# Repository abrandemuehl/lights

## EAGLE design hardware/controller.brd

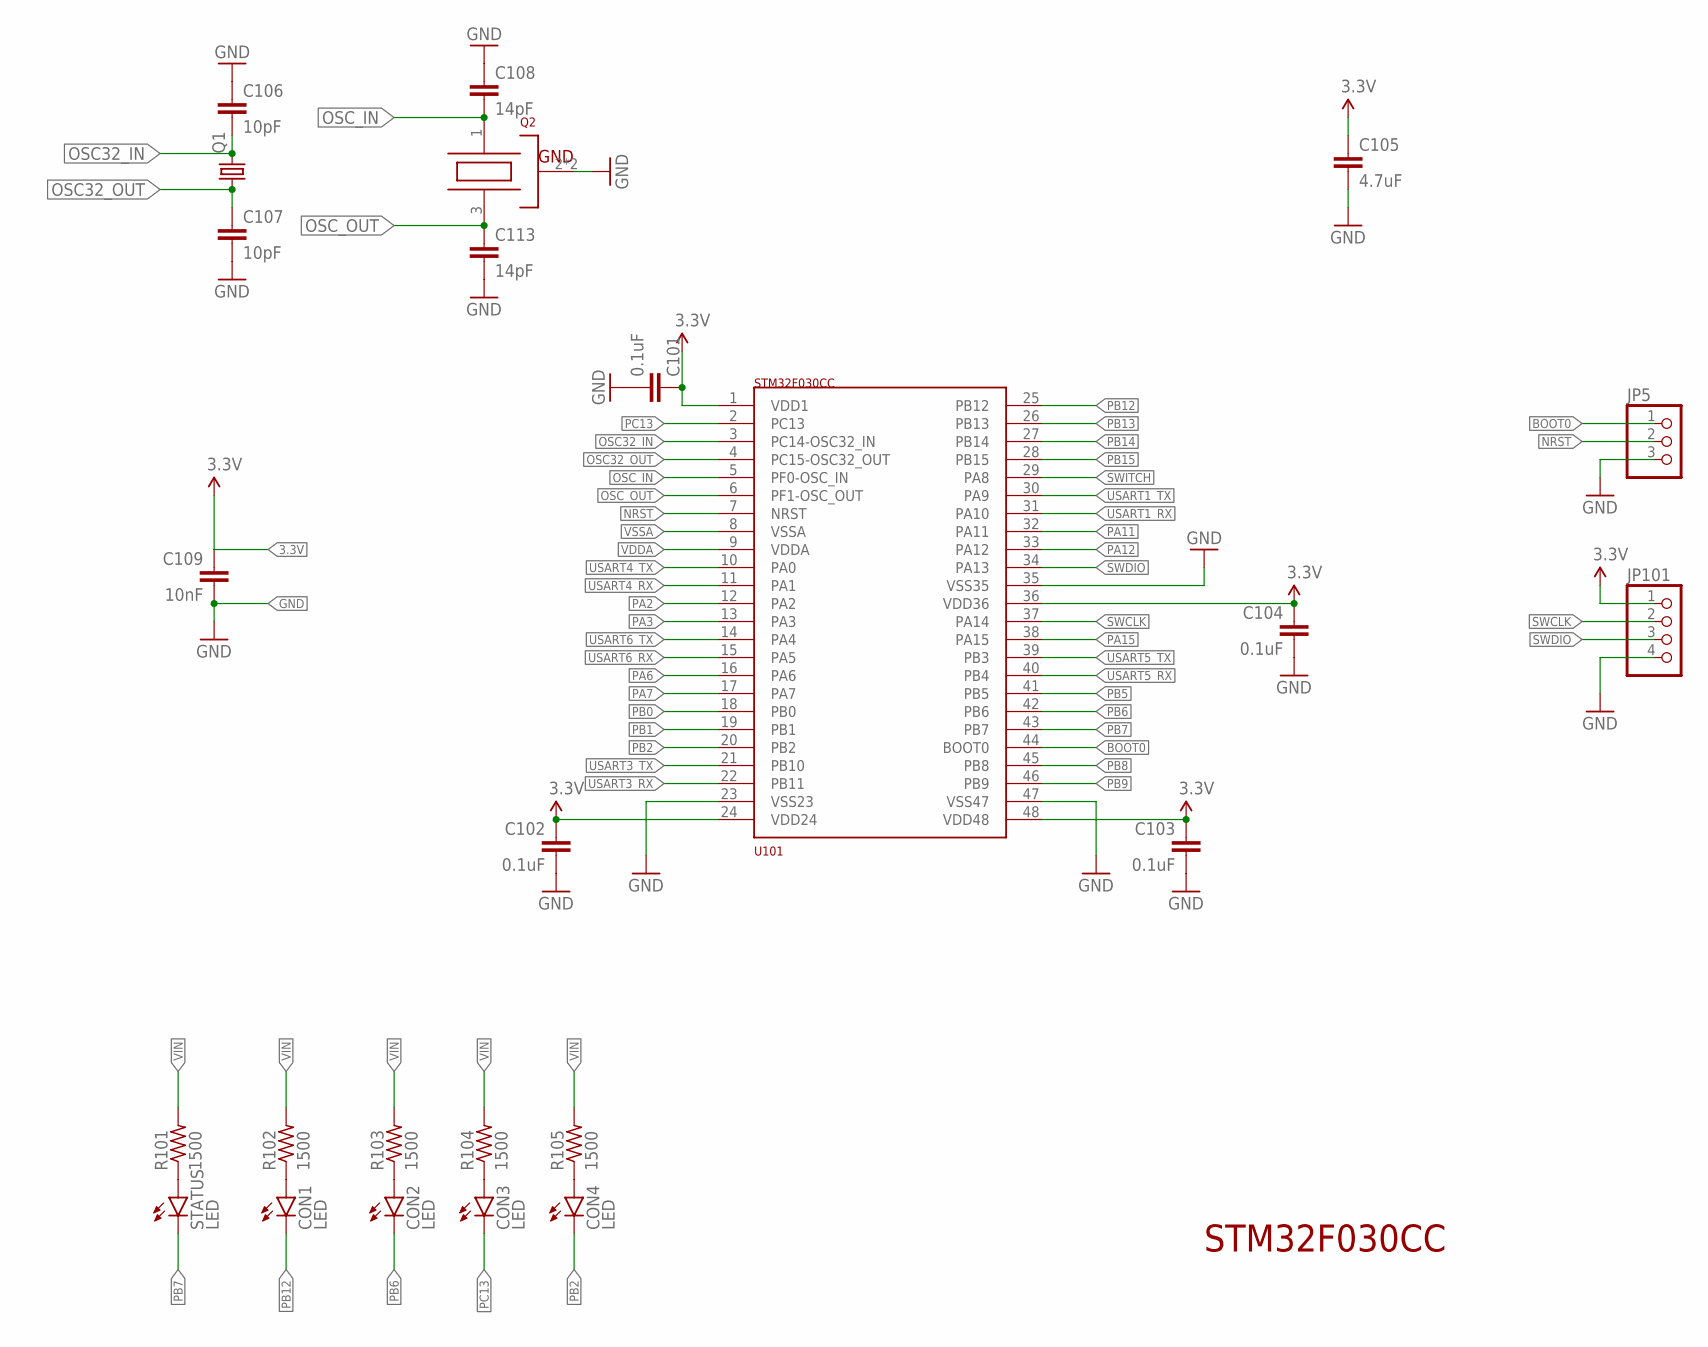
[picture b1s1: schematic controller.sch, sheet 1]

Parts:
C101, C102, C103, C104: 0.1uF; 0603-CAP
C105: 4.7uF; 0603-CAP
C106, C107: 10pF; 0603-CAP
C108, C113: 14pF; 0603-CAP
C109: 10nF; 0603-CAP
CON1, CON2, CON3, CON4: LED; LED-0603
JP5: PINHD-1X3; 1X03
JP101: PINHD-1X4; 1X04
Q1: CRYSTALFC1610AN; FC1610AN
Q2: OSCILLATOR; OSC3.2X2.5
R101, R102, R103, R104, R105: 1500; R0603
STATUS: LED; LED-0603
U101: STM32F030CC

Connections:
3.3V: C101.1, C102.1, C103.1, C104.1, C105.1, C109.1, JP101.1, U101.1 (VDD1), U101.24 (VDD24), U101.36 (VDD36), U101.48 (VDD48); also elsewhere on the board
BOOT0: JP5.1, U101.44 (BOOT0); also elsewhere on the board
GND: C101.2, C102.2, C103.2, C104.2, C105.2, C106.1, C107.2, C108.1, C109.2, C113.2, JP5.3, JP101.4, Q2.2 (GND), Q2.4 (GND), U101.23 (VSS23), U101.35 (VSS35), U101.47 (VSS47); also elsewhere on the board
unnamed: R101.1, STATUS.A
unnamed: CON1.A, R102.1
unnamed: CON2.A, R103.1
unnamed: CON3.A, R104.1
unnamed: CON4.A, R105.1
NRST: JP5.2, U101.7 (NRST); also elsewhere on the board
OSC32_IN: C106.2, Q1.2, U101.3 (PC14-OSC32_IN)
OSC32_OUT: C107.1, Q1.1, U101.4 (PC15-OSC32_OUT)
OSC_IN: C108.2, Q2.1 (OSC1), U101.5 (PF0-OSC_IN)
OSC_OUT: C113.1, Q2.3 (OSC2), U101.6 (PF1-OSC_OUT)
PA2: U101.12 (PA2)
PA3: U101.13 (PA3)
PA6: U101.16 (PA6)
PA7: U101.17 (PA7)
PA11: U101.32 (PA11)
PA12: U101.33 (PA12)
PA15: U101.38 (PA15)
PB0: U101.18 (PB0)
PB1: U101.19 (PB1)
PB2: CON4.C, U101.20 (PB2)
PB5: U101.41 (PB5)
PB6: CON2.C, U101.42 (PB6)
PB7: STATUS.C, U101.43 (PB7)
PB8: U101.45 (PB8)
PB9: U101.46 (PB9)
PB12: CON1.C, U101.25 (PB12)
PB13: U101.26 (PB13)
PB14: U101.27 (PB14)
PB15: U101.28 (PB15)
PC13: CON3.C, U101.2 (PC13)
SWCLK: JP101.2, U101.37 (PA14)
SWDIO: JP101.3, U101.34 (PA13)
SWITCH: U101.29 (PA8); also elsewhere on the board
USART1_RX: U101.31 (PA10); also elsewhere on the board
USART1_TX: U101.30 (PA9); also elsewhere on the board
USART3_RX: U101.22 (PB11); also elsewhere on the board
USART3_TX: U101.21 (PB10); also elsewhere on the board
USART4_RX: U101.11 (PA1); also elsewhere on the board
USART4_TX: U101.10 (PA0); also elsewhere on the board
USART5_RX: U101.40 (PB4); also elsewhere on the board
USART5_TX: U101.39 (PB3); also elsewhere on the board
USART6_RX: U101.15 (PA5); also elsewhere on the board
USART6_TX: U101.14 (PA4); also elsewhere on the board
VDDA: U101.9 (VDDA)
VIN: R101.2, R102.2, R103.2, R104.2, R105.2; also elsewhere on the board
VSSA: U101.8 (VSSA)

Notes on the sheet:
STM32F030CC

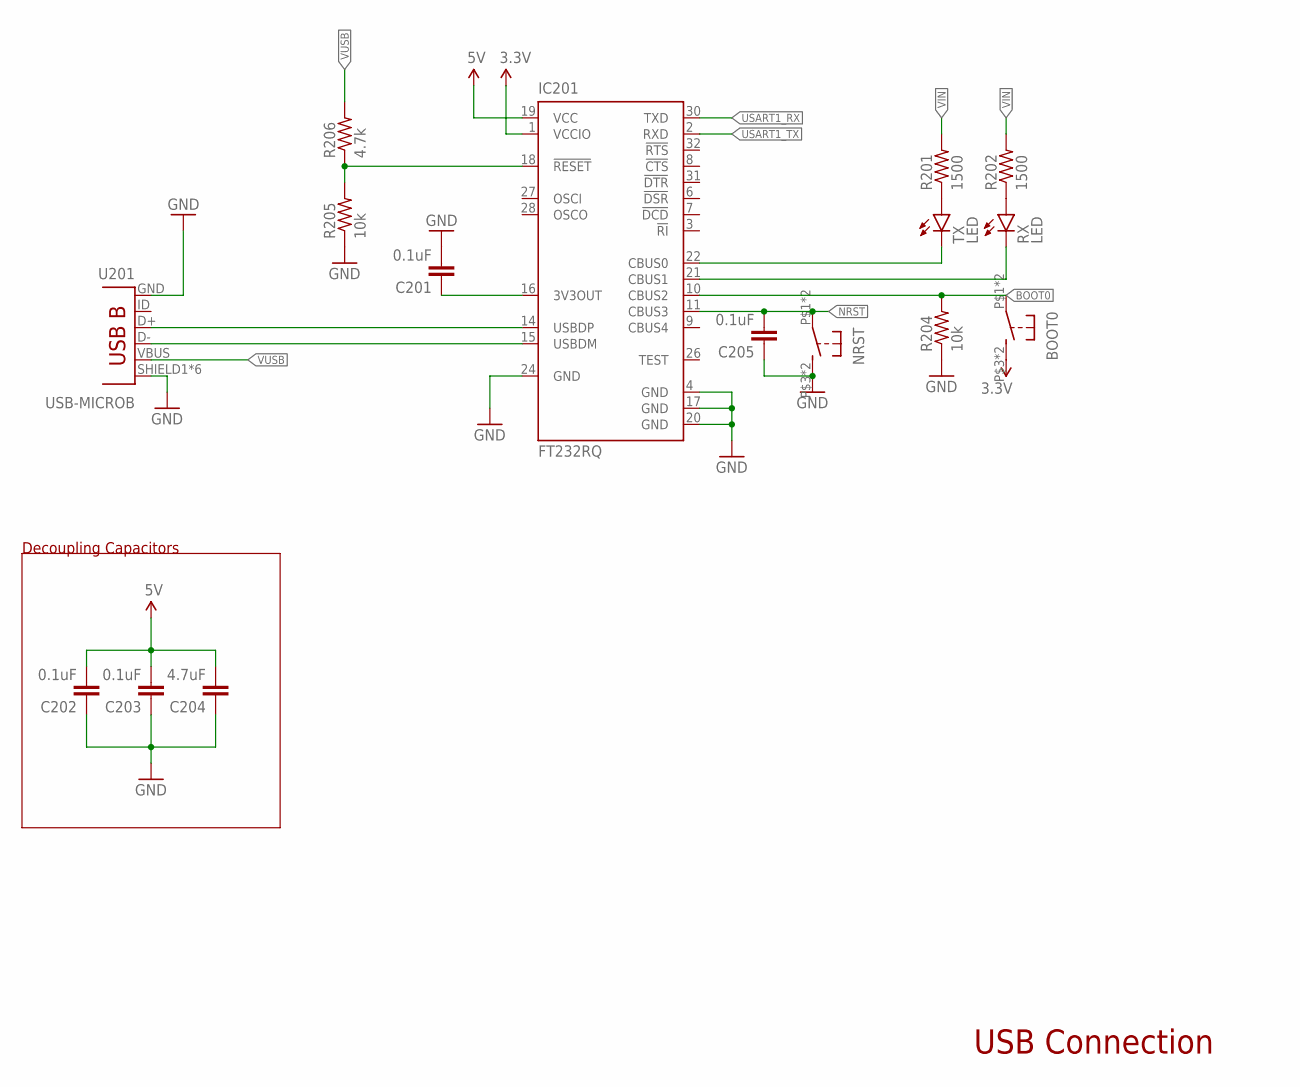
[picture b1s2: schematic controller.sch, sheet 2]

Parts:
BOOT0: BUTTON_MOMENTARY4P; BUTTON_MOMENTARY_KMR211G
C201, C202, C203, C205: 0.1uF; 0603-CAP
C204: 4.7uF; 0603-CAP
IC201: FT232RQ; QFN32
NRST: BUTTON_MOMENTARY4P; BUTTON_MOMENTARY_KMR211G
R201, R202: 1500; R0603
R204, R205: 10k; R0603
R206: 4.7k; R0603
RX: LED; LED-0603
TX: LED; LED-0603
U201: USB-MICROB; USB-B-MICRO-SMD

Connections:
3.3V: BOOT0.P$3 (S), BOOT0.P$4 (S), IC201.1 (VCCIO); also elsewhere on the board
5V: C202.2, C203.2, C204.2, IC201.19 (VCC); also elsewhere on the board
BOOT0: BOOT0.P$1, BOOT0.P$2, IC201.10 (CBUS2), R204.2; also elsewhere on the board
GND: C201.2, C202.1, C203.1, C204.1, C205.1, IC201.4 (GND), IC201.17 (GND), IC201.20 (GND), IC201.24 (GND), NRST.P$3 (S), NRST.P$4 (S), R204.1, R205.1, U201.GND, U201.SHIELD1 (SHIELD), U201.SHIELD2 (SHIELD), U201.SHIELD3 (SHIELD), U201.SHIELD4 (SHIELD), U201.SHIELD5 (SHIELD), U201.SHIELD6 (SHIELD); also elsewhere on the board
unnamed: IC201.18 (!RESET), R205.2, R206.1
unnamed: C201.1, IC201.16 (3V3OUT)
unnamed: R202.1, RX.A
unnamed: R201.1, TX.A
NRST: C205.2, IC201.11 (CBUS3), NRST.P$1, NRST.P$2; also elsewhere on the board
RX_LED: IC201.21 (CBUS1), RX.C
TX_LED: IC201.22 (CBUS0), TX.C
USART1_RX: IC201.30 (TXD); also elsewhere on the board
USART1_TX: IC201.2 (RXD); also elsewhere on the board
USBDM: IC201.15 (USBDM), U201.D-
USBDP: IC201.14 (USBDP), U201.D+
VIN: R201.2, R202.2; also elsewhere on the board
VUSB: R206.2, U201.VBUS

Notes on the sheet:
USB Connection
Decoupling Capacitors

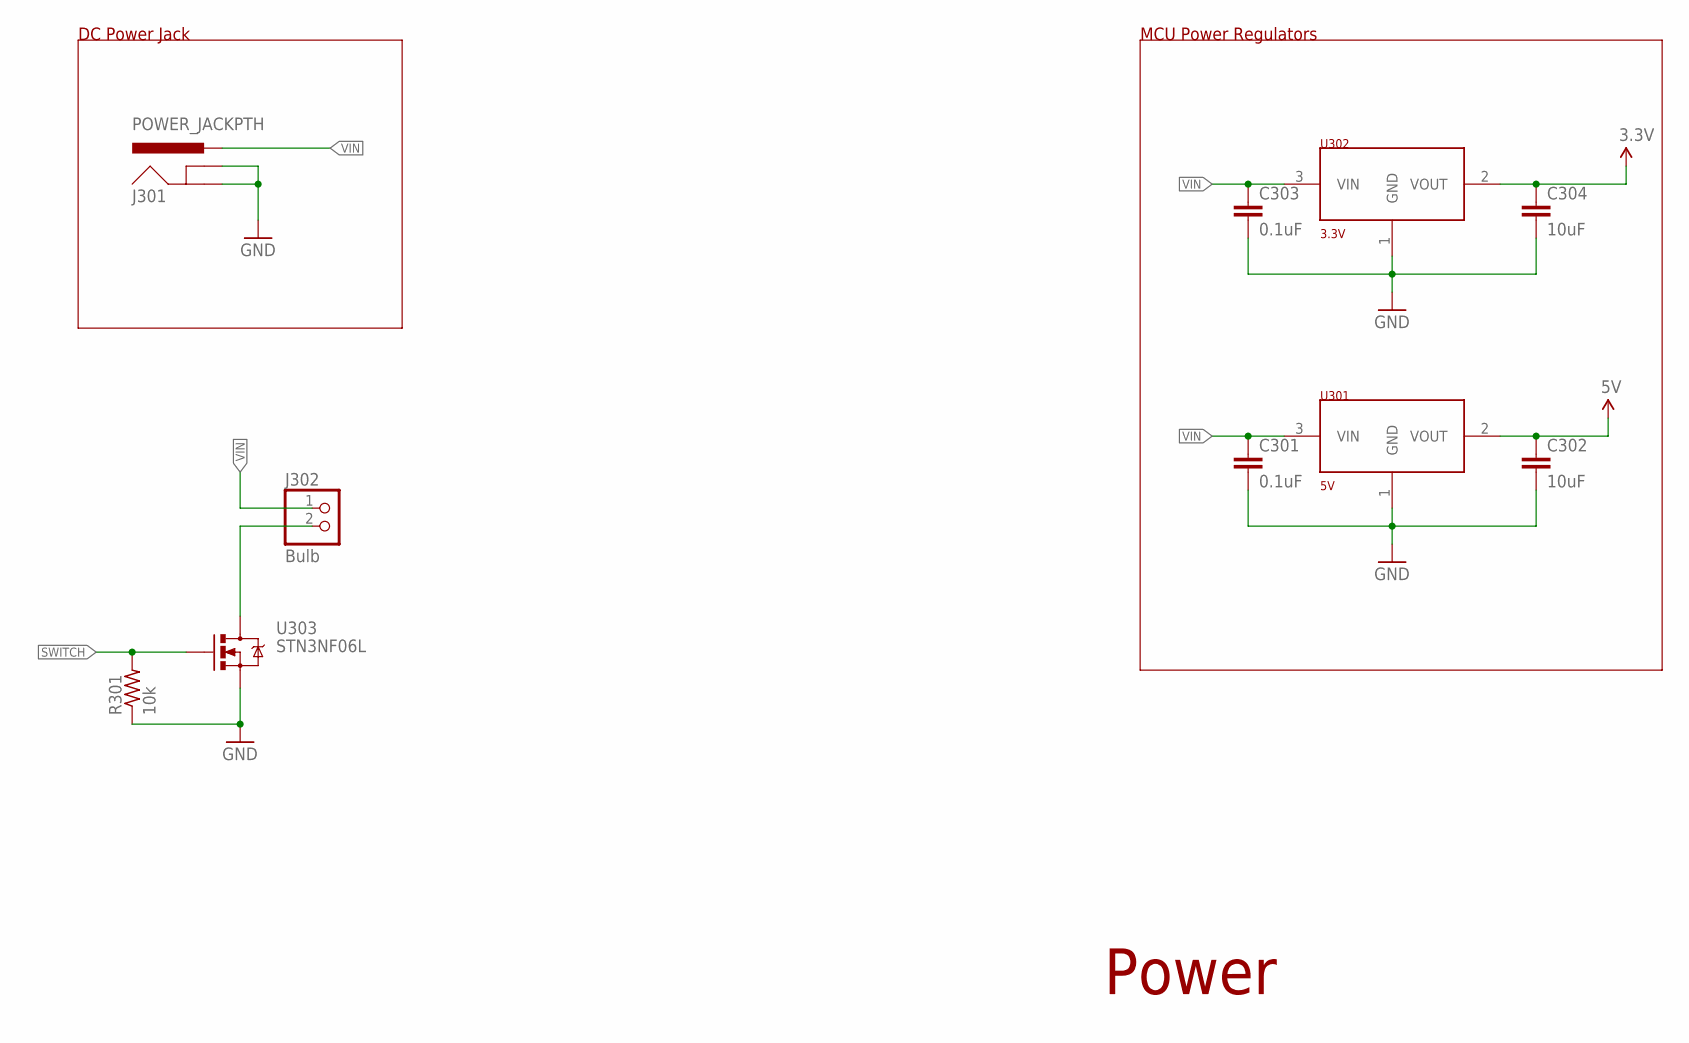
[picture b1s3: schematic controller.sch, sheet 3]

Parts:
C301, C303: 0.1uF; 0603-CAP
C302, C304: 10uF; 0603-CAP
J301: POWER_JACKPTH; POWER_JACK_PTH
J302: Bulb; 1X02
R301: 10k; R0603
U301: 5V; SOT223
U302: 3.3V; SOT223
U303: STN3NF06L; SOT223

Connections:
3.3V: C304.1, U302.2 (VOUT); also elsewhere on the board
5V: C302.1, U301.2 (VOUT); also elsewhere on the board
BULB: J302.2, U303.2 (D), U303.4 (D)
GND: C301.2, C302.2, C303.2, C304.2, J301.GND, J301.GNDBREAK, R301.1, U301.1 (GND), U302.1 (GND), U303.3 (S); also elsewhere on the board
SWITCH: R301.2, U303.1 (G); also elsewhere on the board
VIN: C301.1, C303.1, J301.PWR, J302.1, U301.3 (VIN), U302.3 (VIN); also elsewhere on the board

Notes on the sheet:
Power
MCU Power Regulators
DC Power Jack

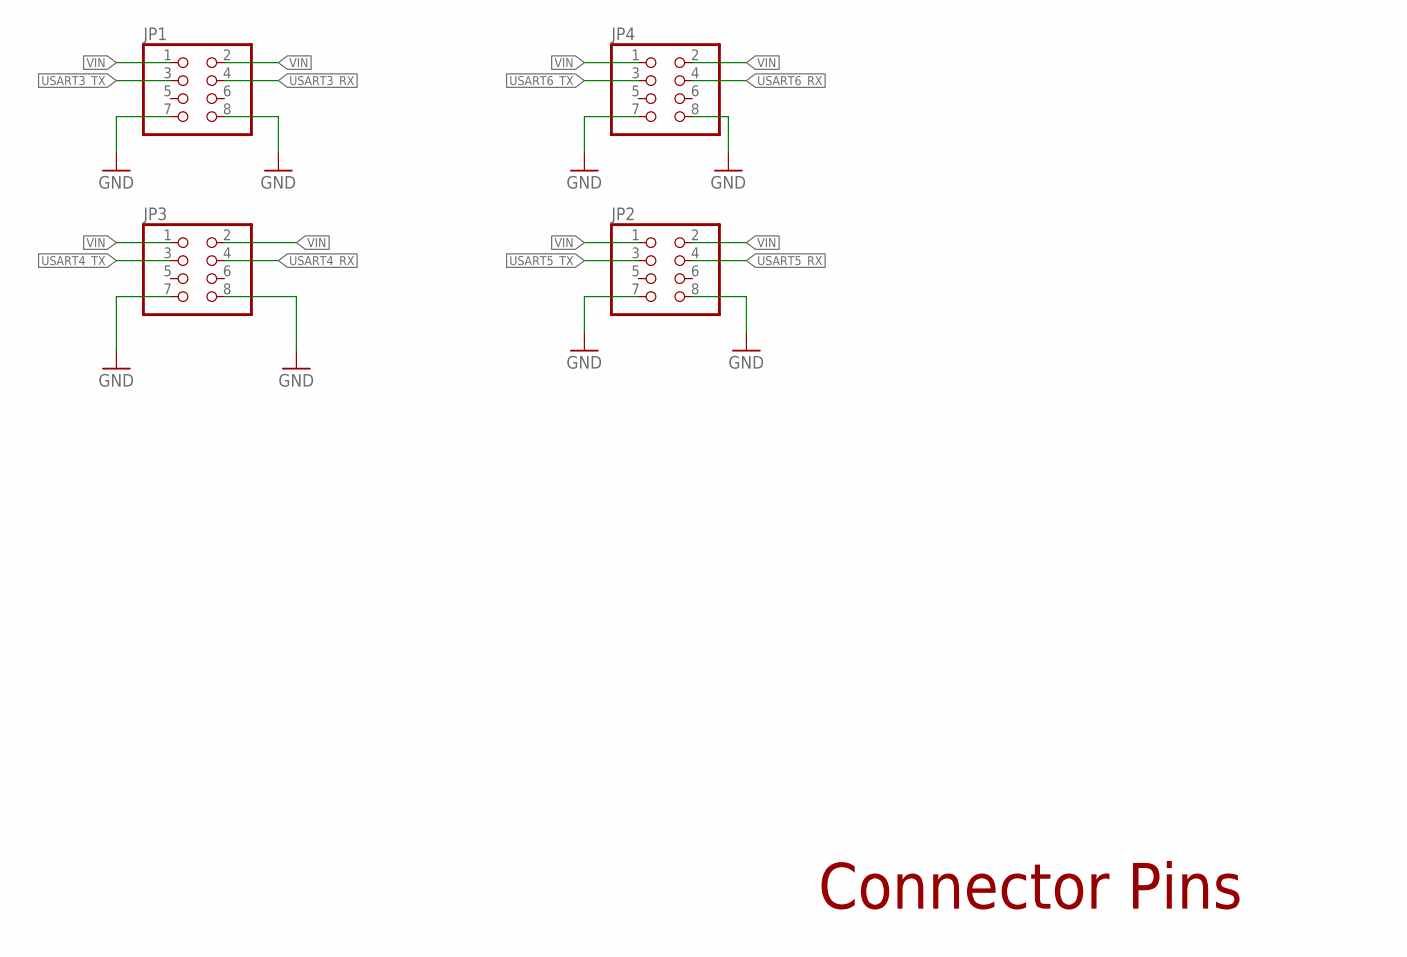
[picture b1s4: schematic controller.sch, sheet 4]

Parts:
JP1, JP2, JP3, JP4: PINHD-2X4; 2X04

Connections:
GND: JP1.7, JP1.8, JP2.7, JP2.8, JP3.7, JP3.8, JP4.7, JP4.8; also elsewhere on the board
USART3_RX: JP1.4; also elsewhere on the board
USART3_TX: JP1.3; also elsewhere on the board
USART4_RX: JP3.4; also elsewhere on the board
USART4_TX: JP3.3; also elsewhere on the board
USART5_RX: JP2.4; also elsewhere on the board
USART5_TX: JP2.3; also elsewhere on the board
USART6_RX: JP4.4; also elsewhere on the board
USART6_TX: JP4.3; also elsewhere on the board
VIN: JP1.1, JP1.2, JP2.1, JP2.2, JP3.1, JP3.2, JP4.1, JP4.2; also elsewhere on the board

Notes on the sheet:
Connector Pins

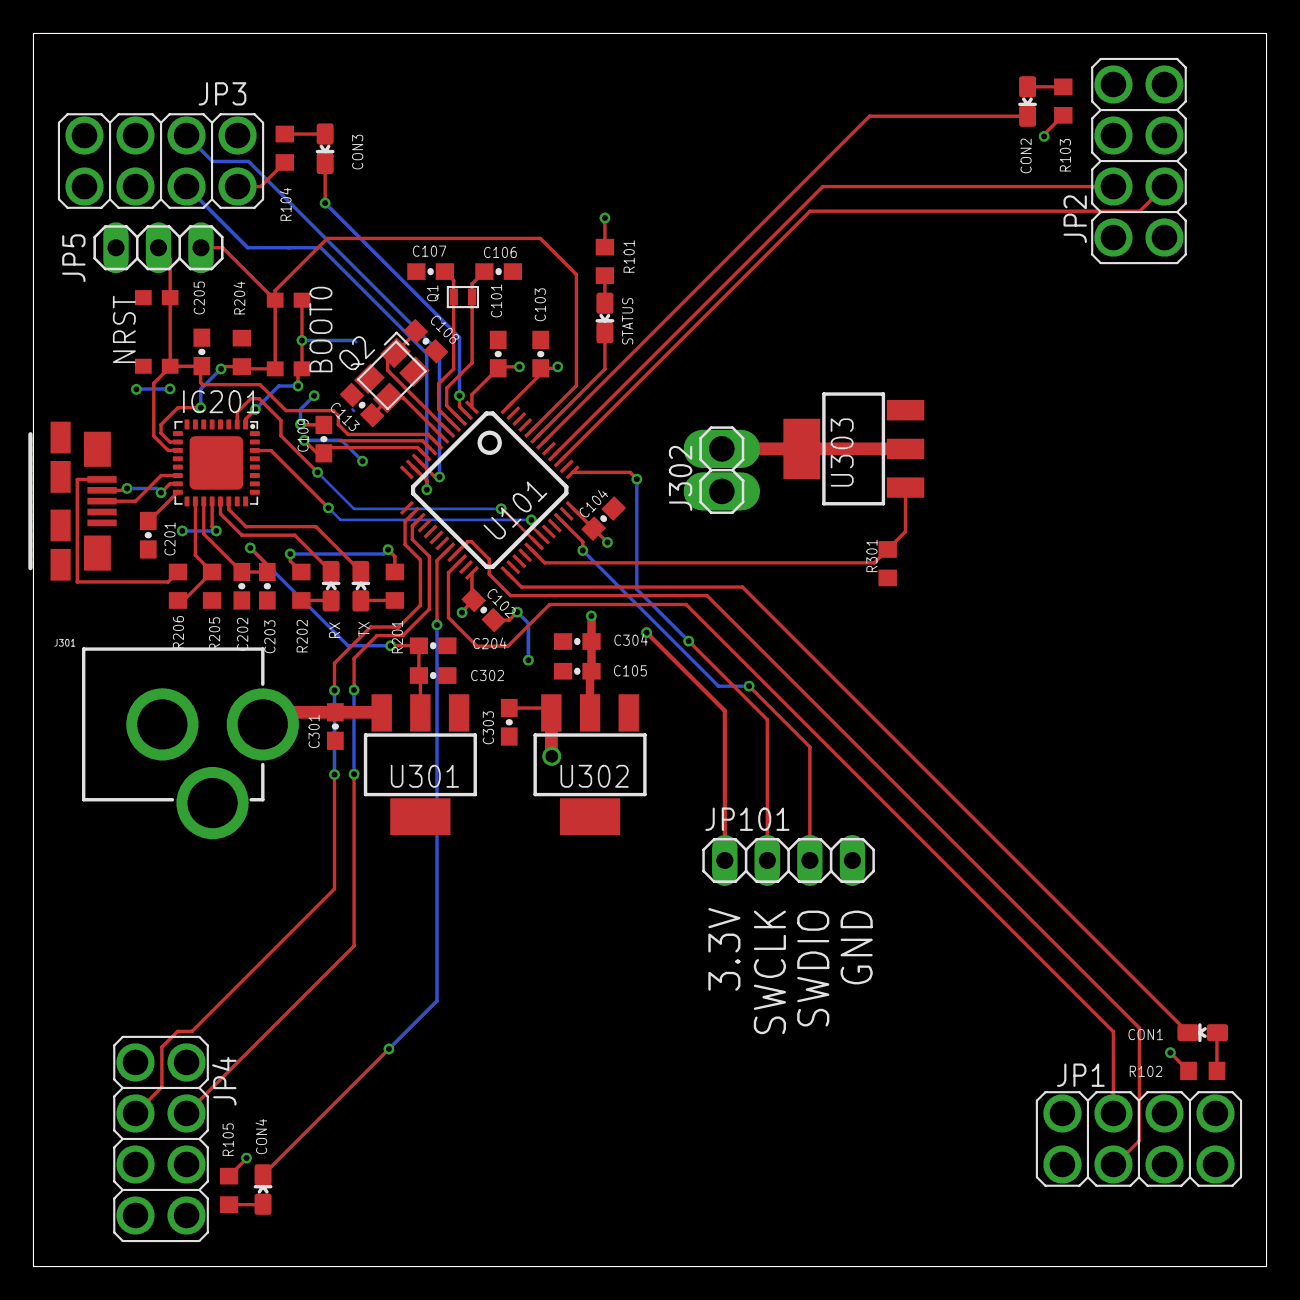
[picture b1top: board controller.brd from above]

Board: 2 copper layers, 73.7 x 73.7 mm, 55 parts (0 on the bottom side), 43 nets.

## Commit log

2018-01-24 Add gitignore
2018-01-24 Add stm32f030cc processor
2018-02-19 Add software
2018-02-20 Fix PLL configuration to multiply HSE by 2 instead of 6
2018-02-20 Fix line endings
2018-02-20 Toggle GPIO pins, use STD_PERIPH startup file
2018-03-06 Set up timer
2018-03-06 Add base controller
2018-03-06 Fix USART1 pins
2018-03-13 Add USART cc classes
2018-03-13 Switch to c++ and use USART class
2018-03-13 Timer progress
2018-03-13 Update makefile
2018-04-16 software temp
2018-04-16 Hardware updates
2018-04-16 Temp
2018-04-19 Add flash command
2018-04-19 Add ftdi patch
2018-04-19 libftdi in readme
2018-04-19 Compiling
2018-04-19 Fix syntax errors
2018-04-23 Commit before changing everything
2018-04-23 Flash status LED
2018-04-23 Stuff necessary for flashing led
2018-04-24 Before rewrite
2018-04-24 Switch to C
2018-04-24 Working echo
2018-04-26 Write to argument usart not USART1
2018-04-26 Sending data between
2018-04-27 Working location sharing
2018-04-27 Synchronization not working
2018-04-27 Synchronization working
2018-04-27 Remove rtc period arg
2018-04-27 readme instructions
2018-04-27 Make leader follower node distinction
2018-04-27 Will now start up reliable
    The leader will take control quickly and work its magic
